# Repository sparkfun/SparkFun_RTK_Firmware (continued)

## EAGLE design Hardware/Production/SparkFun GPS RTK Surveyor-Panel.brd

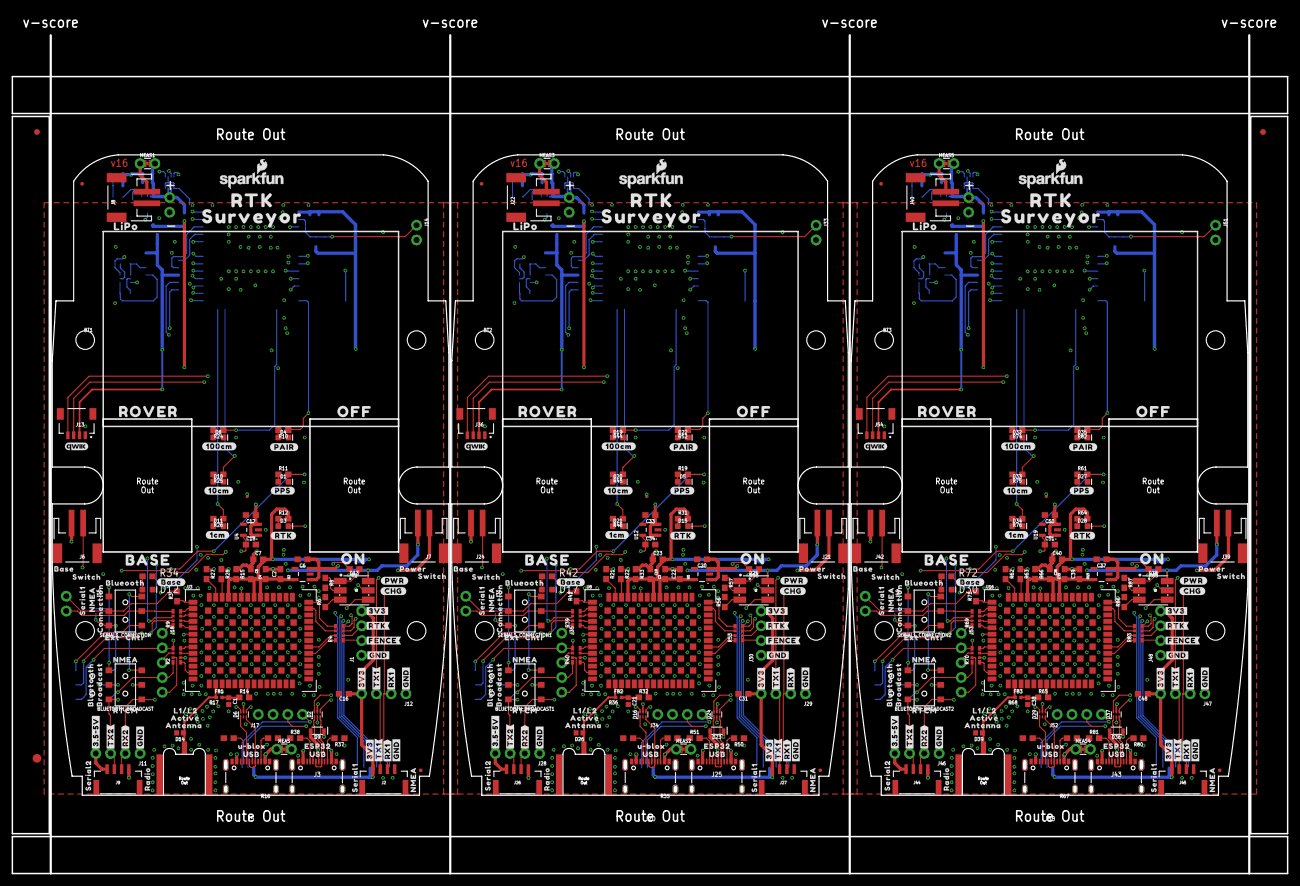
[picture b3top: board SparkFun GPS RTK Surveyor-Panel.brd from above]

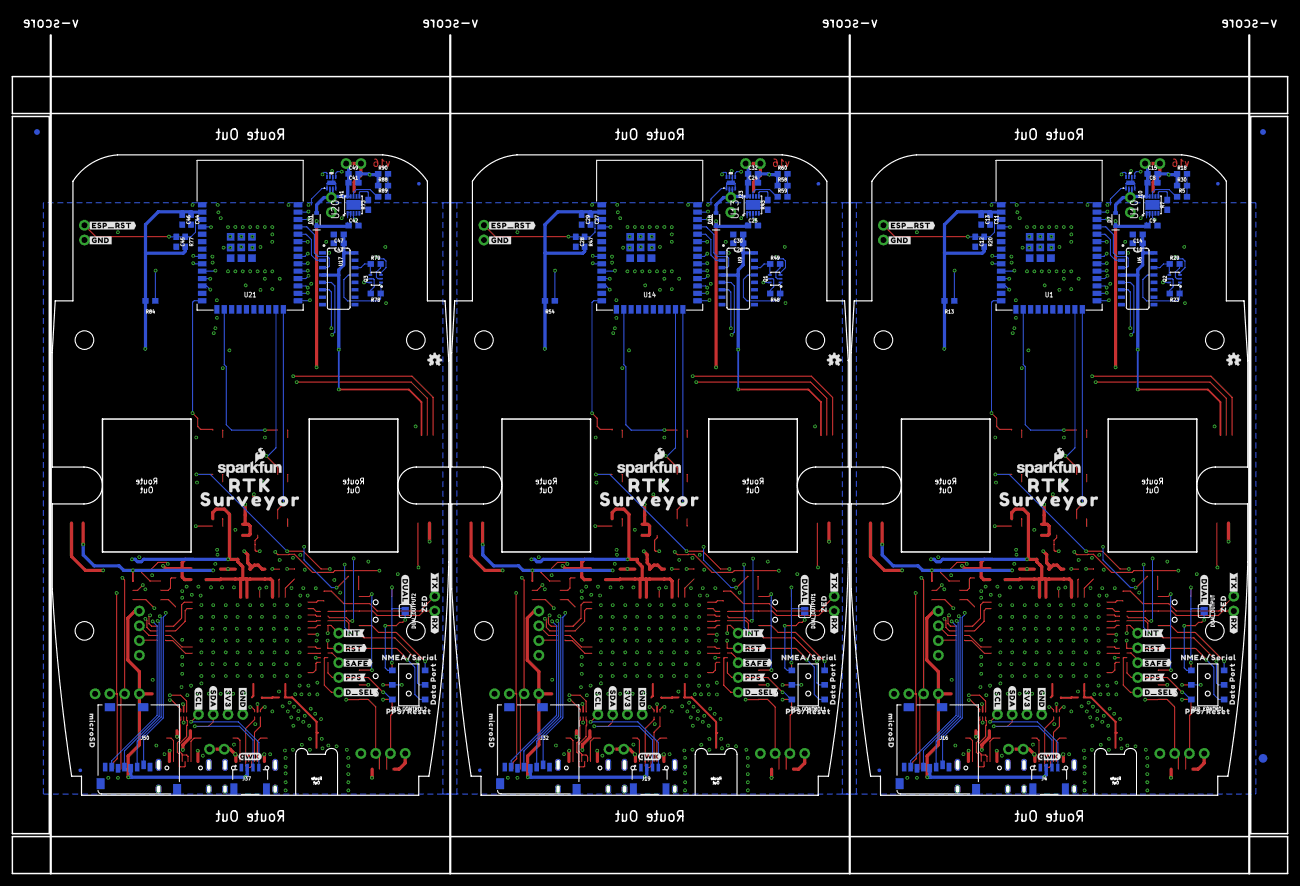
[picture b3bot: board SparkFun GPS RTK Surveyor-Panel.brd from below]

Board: 4 copper layers, 219.3 x 144.2 mm, 588 parts (165 on the bottom side), 285 nets.

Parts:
BLUETOOTH_BROADCAST, BLUETOOTH_BROADCAST1, BLUETOOTH_BROADCAST2: SWITCH_DPDT_SMD_AYZ0202
BT1, BT2, BT3: LIPO-OUTLINE1000; LIPO-1000
C1, C21, C38: 47pF; 0402
C2, C3, C4, C6, C17, C18, C20, C22, C33, C34, C35, C37, C39, C50, C51: 1.0uF; 0603
C5, C7, C11, C12, C13, C15, C16, C19, C23, C27, C28, C29, C31, C32, C36, C40, C44, C45, C46, C48, C49: 0.1uF; 0603
C8, C9, C24, C25, C41, C42: 4.7uF; 0603
C10, C14, C26, C30, C43, C47: 10uF; 0603
D1, D5, D27: Yellow; LED-0603
D2, D6, D16, D24, D29, D37: PRTR5V0U2F; SOT886
D3, D15, D28: WHITE; LED-0603
D4, D22, D35: BLUE; LED-0603
D7, D9, D18, D23, D31, D36: 3A/10V/280mV; SOD-323
D8, D10, D11, D19, D20, D21, D32, D33, D34: GREEN; LED-0603
D12, D17, D30: RED; LED-0603
D13, D25, D38: LED-TRICOLOR-5050
D14, D26, D39: PESD0402; 0402
DUAL_OUTPUT, DUAL_OUTPUT1, DUAL_OUTPUT2: SMT-JUMPER_2_NO_SILK
E1, E2, E3: SMA; SMA-EDGE-SMD
E$1, E$2, E$3, E$4: FIDUCIAL-1X2
E$5, E$6: FIDUCIAL-1.5X3
FB1, FB2, FB3: 2.66Ω; 0402-TIGHT
J1, J11, J12, J28, J29, J30, J46, J47, J48: 1X04_NO_SILK
J2, J9, J26, J27, J44, J45: JST-4-SMD-1.25MM-LOCKING
J3, J5, J20, J25, J38, J43: USB Female Type C Connector; USB-C-16P_4LAYER-PADS
J4, J19, J37: External; JST04_1MM_RA
J6, J24, J42: Start Base; JST-2-SMD
J7, J21, J39: Power Switch; JST-2-SMD
J8, J22, J40: JST-2-SMD
J10, J14, J15, J23, J31, J33, J41, J49, J51: 1X02_NO_SILK
J13, J36, J54: Internal; JST04_1MM_RA
J16, J32, J50: microSD; MICRO-SD-SOCKET
J17, J34, J52: Qwiic Right Angle; 1X04_NO_SILK
J18, J35, J53: 1X05_NO_SILK
JP1, JP2, JP3, JP4, JP5, JP6, JP7, JP8, JP21, JP61, JP71, JP81: FIDUCIALUFIDUCIAL; FIDUCIAL-MICRO
LOGO1, LOGO4, LOGO7: OSHW-LOGOMINI; OSHW-LOGO-MINI
LOGO2, LOGO3, LOGO5, LOGO6, LOGO8, LOGO9: SFE_LOGO_NAME_FLAME.1_INCH; SFE_LOGO_NAME_FLAME_.1
MEAS, MEAS1, MEAS2, MEAS3, MEAS4, MEAS5: COMBO-JUMPER_2_NC_TRACE
Q1, Q2, Q3: MBT3904DW1T1; SC70-6
R1, R55, R85: 4.7k; 0603
R2, R4, R9, R39, R40, R53, R69, R70, R83: 33; 1206_RA
R3, R41, R71: 33; 0603
R5, R59, R89: 0; 0603
R6, R7, R8, R43, R56, R57, R73, R86, R87: 1k; 0603
R10, R12, R31, R34, R42, R52, R64, R72, R82: 330; 0603
R11, R19, R24, R25, R26, R44, R45, R46, R61, R74, R75, R76: 20; 0603
R13, R15, R33, R54, R66, R84: 100k; 0603
R14, R32, R65: 10; 0603
R16, R17, R35, R36, R37, R38, R50, R51, R67, R68, R80, R81: 5.1k; 0603
R18, R20, R23, R29, R47, R48, R49, R60, R77, R78, R79, R90: 10k; 0603
R21, R22, R27, R28, R62, R63: 27; 0603
R30, R58, R88: 150k; 0603
SERIAL1_CONNECTION, SERIAL1_CONNECTION1, SERIAL1_CONNECTION2: SWITCH_DPDT_SMD_AYZ0202
U1, U14, U21: ESP-WROOM-3232D-NARROW; ESP-WROOM-32D-NARROW
U2, U4, U5, U12, U15, U19: 3.3V; SOT23-5
U3, U8, U16: U-BLOX_ZED-F9P; ZED-F9P
U6, U9, U17: CH340C; SO016
U7, U11, U18: MAX17048; DFN-8
U10, U13, U20: MCP73833; DFN-10
U$1, U$38, U$48, U$82, U$98, U$126, U$127, U$169, U$190, U$218, U$219, U$261: #GND#0
U$2, U$30, U$93, U$184, U$185, U$276: QWIIC_4MM
U$3, U$34, U$112, U$114, U$204, U$206: ROCKER_SWITCH
U$4, U$113, U$205: #BASE#0
U$5, U$37, U$47, U$97, U$125, U$166, U$189, U$217, U$258: #3V3#0
U$6, U$99, U$191: ANTENNA0
U$7, U$74, U$173, U$174, U$265, U$266: RTK0
U$8, U$106, U$198: #CHG#0
U$9, U$71, U$100, U$151, U$192, U$243: _SURVEYOR3
U$10, U$101, U$193: #RTK#1
U$11, U$150, U$242: #PPS#0
U$12, U$94, U$186: #RTK#0
U$13, U$15, U$21, U$69, U$75, U$76, U$77, U$78, U$115, U$116, U$149, U$156, U$157, U$158, U$159, U$160, U$207, U$208, U$241, U$248, U$249, U$250, U$251, U$252: LIGHT_PIPE_3MM
U$14, U$152, U$244: #RX#2
U$16, U$153, U$245: ZED0
U$17, U$131, U$223: ##SAFE##5
U$18, U$102, U$194: ACTIVE0
U$19, U$103, U$195: L1#L21
U$20, U$104, U$196: #PAIR#0
U$22, U$117, U$209: BASE2
U$23, U$138, U$230: #3#5#5V#0
U$24, U$95, U$187: #PPS#1
U$25, U$96, U$188: #PWR#2
U$26, U$105, U$197: 1553DBK-ENCLOSURE
U$27, U$107, U$199: LIPO0
U$28, U$130, U$222: ##RST##4
U$29, U$63, U$111, U$147, U$203, U$239: SERIAL10
U$31, U$118, U$210: OFF1
U$32, U$132, U$224: #FENCE#3
U$33, U$133, U$225: #INT#0
U$35, U$108, U$200: U#BLOX0
U$36, U$66, U$109, U$164, U$201, U$256: USB1
U$39, U$121, U$213: #RX2#2
U$40, U$122, U$214: #TX2#1
U$41, U$139, U$231: BLUETOOTH2
U$42, U$119, U$211: ON0
U$43, U$110, U$202: SERIAL20
U$44, U$120, U$212: ROVER3
U$45, U$68, U$123, U$168, U$215, U$260: #RX1#2
U$46, U$65, U$124, U$167, U$216, U$259: #TX1#1
U$49, U$52, U$128, U$141, U$220, U$233: NMEA1
U$50, U$129, U$221: RADIO0
U$51, U$140, U$232: BROADCAST3
U$53, U$142, U$234: RTCM0
U$54, U$134, U$226: BASE0
U$55, U$57, U$135, U$137, U$227, U$229: SWITCH1
U$56, U$136, U$228: POWER0
U$58, U$143, U$235: BLUEOOTH3
U$59, U$144, U$236: CNTR1
U$60, U$172, U$264: #ESP_RST#0
U$61, U$145, U$237: EXT0
U$62, U$146, U$238: NMEA2
U$64, U$148, U$240: CONNECTION1
U$67, U$165, U$257: ESP320
U$70, U$175, U$267: #GND#2
U$72, U$154, U$246: #TX#1
U$73, U$155, U$247: #DUAL#0
U$79, U$161, U$253: #1CM#0
U$80, U$162, U$254: #10CM#1
U$81, U$163, U$255: #100CM#2
U$83, U$170, U$262: MICROSD0
U$84, U$171, U$263: #GND#1
U$85, U$176, U$268: #3V3#2
U$86, U$177, U$269: #SCL#1
U$87, U$178, U$270: #SDA#0
U$88, U$179, U$271: #D_SEL#0
U$89, U$180, U$272: DATA2
U$90, U$181, U$273: PORT3
U$91, U$182, U$274: PPS#RESET0
U$92, U$183, U$275: NMEA#SERIAL1
ZED_CONTROL, ZED_CONTROL1, ZED_CONTROL2: SWITCH_DPDT_SMD_AYZ0202

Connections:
3.3V: C2.1, C4.1, C5.2, C7.2, C10.1, C11.1, C13.1, C14.1, C16.1, J1.4, J2.1, J4.2, J12.4, J13.2, J16.VCC, J17.2, R12.2, R13.2, R15.2, R20.2, U1.2, U2.5, U3.33, U3.34, U3.38, U6.4, U6.16
3.3V1: C3.1, C19.2, C22.1, C23.2, C26.1, C27.1, C29.1, C30.1, C31.1, J19.2, J27.1, J29.4, J30.4, J32.VCC, J34.2, J36.2, R31.2, R33.2, R47.2, R54.2, U5.5, U8.33, U8.34, U8.38, U9.4, U9.16, U14.2
3.3V2: C35.1, C36.2, C39.1, C40.2, C43.1, C44.1, C46.1, C47.1, C48.1, J37.2, J45.1, J47.4, J48.4, J50.VCC, J52.2, J54.2, R64.2, R66.2, R77.2, R84.2, U15.5, U16.33, U16.34, U16.38, U17.4, U17.16, U21.2
5V: C6.1, J7.1, J9.1, J11.4, U2.1, U2.3
5V1: C20.1, J21.1, J26.1, J28.4, U5.1, U5.3
5V2: C37.1, J39.1, J44.1, J46.4, U15.1, U15.3
ANT_VCC: C1.1, FB1.2, R14.1
ANT_VCC1: C21.1, FB2.2, R32.1
ANT_VCC2: C38.1, FB3.2, R65.1
BACKUP: C18.1, U3.36, U4.5
BACKUP1: C34.1, U8.36, U12.5
BACKUP2: C51.1, U16.36, U19.5
CC1: J5.A5, R17.2
CC2: J5.B5, R16.2
CC3: J3.B5, R37.2
CC4: J3.A5, R38.2
CC5: J20.A5, R36.2
CC6: J20.B5, R35.2
CC7: J25.B5, R50.2
CC8: J25.A5, R51.2
CC9: J38.A5, R68.2
CC10: J38.B5, R67.2
CC11: J43.B5, R80.2
CC12: J43.A5, R81.2
CHG_LED: R1.2, U10.3
CHG_LED1: R55.2, U13.3
CHG_LED2: R85.2, U20.3
CHG_THERM1: R5.2, R18.2, R30.2
CHG_THERM2: R58.2, R59.2, R60.2
CHG_THERM3: R88.2, R89.2, R90.2
D+: D6.4, R27.1
D+1: D2.4, U6.5
D+2: D16.4, R21.1
D+3: D24.4, U9.5
D+4: D29.4, R62.1
D+5: D37.4, U17.5
D-: D6.6, R28.1
D-1: D2.6, U6.6
D-2: D16.6, R22.1
D-3: D24.6, U9.6
D-4: D29.6, R63.1
D-5: D37.6, U17.6
ESP32_!DTR: Q2.1, R23.1, U6.13
ESP32_!DTR1: Q1.1, R48.1, U9.13
ESP32_!DTR2: Q3.1, R78.1, U17.13
ESP32_!RTS: Q2.4, R29.1, U6.14
ESP32_!RTS1: Q1.4, R49.1, U9.14
ESP32_!RTS2: Q3.4, R79.1, U17.14
ESP32_EN: C12.1, J14.1, Q2.3, R20.1, U1.3
ESP32_EN1: C28.1, J33.1, Q1.3, R47.1, U14.3
ESP32_EN2: C45.1, J51.1, Q3.3, R77.1, U21.3
ESP32_RXI: U1.34, U6.2
ESP32_RXI1: U9.2, U14.34
ESP32_RXI2: U17.2, U21.34
ESP32_TXO: U1.35, U6.3
ESP32_TXO1: U9.3, U14.35
ESP32_TXO2: U17.3, U21.35
ESP_0/BOOT: Q2.6, U1.25
ESP_0/BOOT1: Q1.6, U14.25
ESP_0/BOOT2: Q3.6, U21.25
ESP_2/LED_1CM: R26.1, U1.24
ESP_2/LED_1CM1: R46.1, U14.24
ESP_2/LED_1CM2: R76.1, U21.24
ESP_4/LED_BASE_STAT: R34.1, U1.26
ESP_4/LED_BASE_STAT1: R42.1, U14.26
ESP_4/LED_BASE_STAT2: R72.1, U21.26
ESP_5/SWITCH_BASE_SELECT: J6.1, U1.29
ESP_5/SWITCH_BASE_SELECT1: J24.1, U14.29
ESP_5/SWITCH_BASE_SELECT2: J42.1, U21.29
ESP_12/LED_BLUETOOTH: R10.1, U1.14
ESP_12/LED_BLUETOOTH1: R52.1, U14.14
ESP_12/LED_BLUETOOTH2: R82.1, U21.14
ESP_13/LED_100CM: R24.1, U1.16
ESP_13/LED_100CM1: R44.1, U14.16
ESP_13/LED_100CM2: R74.1, U21.16
ESP_15/LED_10CM: R25.1, U1.23
ESP_15/LED_10CM1: R45.1, U14.23
ESP_15/LED_10CM2: R75.1, U21.23
ESP_16/BT_RXI: BLUETOOTH_BROADCAST.2, U1.27
ESP_16/BT_RXI1: BLUETOOTH_BROADCAST1.2, U14.27
ESP_16/BT_RXI2: BLUETOOTH_BROADCAST2.2, U21.27
ESP_17/BT_TXO: BLUETOOTH_BROADCAST.5, U1.28
ESP_17/BT_TXO1: BLUETOOTH_BROADCAST1.5, U14.28
ESP_17/BT_TXO2: BLUETOOTH_BROADCAST2.5, U21.28
ESP_18/SD_SCK: J16.SCLK, U1.30
ESP_18/SD_SCK1: J32.SCLK, U14.30
ESP_18/SD_SCK2: J50.SCLK, U21.30
ESP_19/SD_CIPO: J16.DO/DAT0, U1.31
ESP_19/SD_CIPO1: J32.DO/DAT0, U14.31
ESP_19/SD_CIPO2: J50.DO/DAT0, U21.31
ESP_21/SDA: J4.3, J13.3, J17.3, R9.P6, U1.33, U7.8
ESP_21/SDA1: J19.3, J34.3, J36.3, R39.P6, U11.8, U14.33
ESP_21/SDA2: J37.3, J52.3, J54.3, R69.P6, U18.8, U21.33
ESP_22/SCL: J4.4, J13.4, J17.4, R9.P7, U1.36, U7.7
ESP_22/SCL1: J19.4, J34.4, J36.4, R39.P7, U11.7, U14.36
ESP_22/SCL2: J37.4, J52.4, J54.4, R69.P7, U18.7, U21.36
ESP_23/SD_COPI: J16.DI/CMD, U1.37
ESP_23/SD_COPI1: J32.DI/CMD, U14.37
ESP_23/SD_COPI2: J50.DI/CMD, U21.37
ESP_25/SD_!CS!: J16.CS/DAT3, R13.1, U1.10
ESP_25/SD_!CS!1: J32.CS/DAT3, R54.1, U14.10
ESP_25/SD_!CS!2: J50.CS/DAT3, R84.1, U21.10
ESP_26/ZED_TX_READY: J18.1, R9.P8, U1.11
ESP_26/ZED_TX_READY1: J35.1, R39.P8, U14.11
ESP_26/ZED_TX_READY2: J53.1, R69.P8, U21.11
ESP_26/ZED_TX_READY_LV: R9.P1, U3.46
ESP_26/ZED_TX_READY_LV1: R39.P1, U8.46
ESP_26/ZED_TX_READY_LV2: R69.P1, U16.46
ESP_27/ZED_!RESET!: J18.2, R2.P5, U1.12, ZED_CONTROL.4
ESP_27/ZED_!RESET!1: J35.2, R40.P5, U14.12, ZED_CONTROL1.4
ESP_27/ZED_!RESET!2: J53.2, R70.P5, U21.12, ZED_CONTROL2.4
ESP_27/ZED_!RESET!_LV: R2.P4, U3.49
ESP_27/ZED_!RESET!_LV1: R40.P4, U8.49
ESP_27/ZED_!RESET!_LV2: R70.P4, U16.49
ESP_32/PWR_LVL_RED: D13.5, U1.8
ESP_32/PWR_LVL_RED1: D25.5, U14.8
ESP_32/PWR_LVL_RED2: D38.5, U21.8
ESP_33/PWR_LVL_GRN: D13.4, U1.9
ESP_33/PWR_LVL_GRN1: D25.4, U14.9
ESP_33/PWR_LVL_GRN2: D38.4, U21.9
ESP_36/BATT_ALRT: U1.4, U7.5
ESP_36/BATT_ALRT1: U11.5, U14.4
ESP_36/BATT_ALRT2: U18.5, U21.4
ESP_D1+: D2.3, J3.A6, J3.B6
ESP_D1+1: D24.3, J25.A6, J25.B6
ESP_D1+2: D37.3, J43.A6, J43.B6
ESP_D1-: D2.1, J3.A7, J3.B7
ESP_D1-1: D24.1, J25.A7, J25.B7
ESP_D1-2: D37.1, J43.A7, J43.B7
EXTERNAL_SERIAL1_RXI: SERIAL1_CONNECTION.4, ZED_CONTROL.6
EXTERNAL_SERIAL1_RXI1: SERIAL1_CONNECTION1.4, ZED_CONTROL1.6
EXTERNAL_SERIAL1_RXI2: SERIAL1_CONNECTION2.4, ZED_CONTROL2.6
EXTERNAL_SERIAL1_RXI/ZED_!RESET!: J2.3, J12.2, ZED_CONTROL.5
EXTERNAL_SERIAL1_RXI/ZED_!RESET!1: J27.3, J29.2, ZED_CONTROL1.5
EXTERNAL_SERIAL1_RXI/ZED_!RESET!2: J45.3, J47.2, ZED_CONTROL2.5
EXTERNAL_SERIAL1_TXO: DUAL_OUTPUT.2, SERIAL1_CONNECTION.1, ZED_CONTROL.3
EXTERNAL_SERIAL1_TXO1: DUAL_OUTPUT1.2, SERIAL1_CONNECTION1.1, ZED_CONTROL1.3
EXTERNAL_SERIAL1_TXO2: DUAL_OUTPUT2.2, SERIAL1_CONNECTION2.1, ZED_CONTROL2.3
EXTERNAL_SERIAL1_TXO/PPS: J2.2, J12.3, ZED_CONTROL.2
EXTERNAL_SERIAL1_TXO/PPS1: J27.2, J29.3, ZED_CONTROL1.2
EXTERNAL_SERIAL1_TXO/PPS2: J45.2, J47.3, ZED_CONTROL2.2
FENCE_LV: R4.P8, U3.19
FENCE_LV1: R53.P8, U8.19
FENCE_LV2: R83.P8, U16.19
GND: C1.2, C2.2, C4.2, C5.1, C6.2, C7.1, C8.2, C9.2, C10.2, C11.2, C12.2, C13.2, C14.2, C15.2, C16.2, C17.2, C18.2, D1.C, D2.2, D4.C, D6.2, D8.C, D10.C, D11.C, D12.C, D14.2, E1.GND@0, E1.GND@1, J1.1, J2.4, J3.GND, J3.GND2, J3.SHLD1, J3.SHLD2, J3.SHLD3, J3.SHLD4, J4.1, J5.GND, J5.GND2, J5.SHLD1, J5.SHLD2, J5.SHLD3, J5.SHLD4, J6.2, J8.1, J9.4, J10.2, J11.1, J12.1, J13.1, J14.2, J16.CD1, J16.GND, J16.GND1, J16.GND3, J17.1, R6.2, R7.1, R8.2, R15.1, R16.1, R17.1, R18.1, R30.1, R37.1, R38.1, U1.1, U1.15, U1.38, U1.GND1, U1.GNDT1, U1.GNDT2, U1.GNDT3, U1.GNDT4, U1.GNDT5, U1.GNDT6, U1.GNDT7, U1.GNDT8, U2.2, U3.1, U3.3, U3.12, U3.14, U3.32, U3.37, U3.41, U3.48, U3.55, U3.56, U3.57, U3.58, U3.59, U3.60, U3.61, U3.62, U3.63, U3.64, U3.65, U3.66, U3.67, U3.68, U3.69, U3.70, U3.71, U3.72, U3.73, U3.74, U3.75, U3.76, U3.77, U3.78, U3.79, U3.80, U3.81, U3.82, U3.83, U3.84, U3.85, U3.86, U3.87, U3.88, U3.89, U3.90, U3.91, U3.92, U3.93, U3.94, U3.95, U3.96, U3.97, U3.98, U3.99, U3.100, U3.101, U3.102, U4.2, U6.1, U7.1, U7.4, U7.6, U7.9, U10.5, U10.11
GND1: C3.2, C19.1, C20.2, C21.2, C22.2, C23.1, C24.2, C25.2, C26.2, C27.2, C28.2, C29.2, C30.2, C31.2, C32.2, C33.2, C34.2, D5.C, D16.2, D17.C, D19.C, D20.C, D21.C, D22.C, D24.2, D26.2, E2.GND@0, E2.GND@1, J19.1, J20.GND, J20.GND2, J20.SHLD1, J20.SHLD2, J20.SHLD3, J20.SHLD4, J22.1, J23.2, J24.2, J25.GND, J25.GND2, J25.SHLD1, J25.SHLD2, J25.SHLD3, J25.SHLD4, J26.4, J27.4, J28.1, J29.1, J30.1, J32.CD1, J32.GND, J32.GND1, J32.GND3, J33.2, J34.1, J36.1, R33.1, R35.1, R36.1, R43.1, R50.1, R51.1, R56.2, R57.2, R58.1, R60.1, U5.2, U8.1, U8.3, U8.12, U8.14, U8.32, U8.37, U8.41, U8.48, U8.55, U8.56, U8.57, U8.58, U8.59, U8.60, U8.61, U8.62, U8.63, U8.64, U8.65, U8.66, U8.67, U8.68, U8.69, U8.70, U8.71, U8.72, U8.73, U8.74, U8.75, U8.76, U8.77, U8.78, U8.79, U8.80, U8.81, U8.82, U8.83, U8.84, U8.85, U8.86, U8.87, U8.88, U8.89, U8.90, U8.91, U8.92, U8.93, U8.94, U8.95, U8.96, U8.97, U8.98, U8.99, U8.100, U8.101, U8.102, U9.1, U11.1, U11.4, U11.6, U11.9, U12.2, U13.5, U13.11, U14.1, U14.15, U14.38, U14.GND1, U14.GNDT1, U14.GNDT2, U14.GNDT3, U14.GNDT4, U14.GNDT5, U14.GNDT6, U14.GNDT7, U14.GNDT8
GND2: C35.2, C36.1, C37.2, C38.2, C39.2, C40.1, C41.2, C42.2, C43.2, C44.2, C45.2, C46.2, C47.2, C48.2, C49.2, C50.2, C51.2, D27.C, D29.2, D30.C, D32.C, D33.C, D34.C, D35.C, D37.2, D39.2, E3.GND@0, E3.GND@1, J37.1, J38.GND, J38.GND2, J38.SHLD1, J38.SHLD2, J38.SHLD3, J38.SHLD4, J40.1, J41.2, J42.2, J43.GND, J43.GND2, J43.SHLD1, J43.SHLD2, J43.SHLD3, J43.SHLD4, J44.4, J45.4, J46.1, J47.1, J48.1, J50.CD1, J50.GND, J50.GND1, J50.GND3, J51.2, J52.1, J54.1, R66.1, R67.1, R68.1, R73.1, R80.1, R81.1, R86.2, R87.2, R88.1, R90.1, U15.2, U16.1, U16.3, U16.12, U16.14, U16.32, U16.37, U16.41, U16.48, U16.55, U16.56, U16.57, U16.58, U16.59, U16.60, U16.61, U16.62, U16.63, U16.64, U16.65, U16.66, U16.67, U16.68, U16.69, U16.70, U16.71, U16.72, U16.73, U16.74, U16.75, U16.76, U16.77, U16.78, U16.79, U16.80, U16.81, U16.82, U16.83, U16.84, U16.85, U16.86, U16.87, U16.88, U16.89, U16.90, U16.91, U16.92, U16.93, U16.94, U16.95, U16.96, U16.97, U16.98, U16.99, U16.100, U16.101, U16.102, U17.1, U18.1, U18.4, U18.6, U18.9, U19.2, U20.5, U20.11, U21.1, U21.15, U21.38, U21.GND1, U21.GNDT1, U21.GNDT2, U21.GNDT3, U21.GNDT4, U21.GNDT5, U21.GNDT6, U21.GNDT7, U21.GNDT8
GPS_ANT1: D14.1, E1.SIG, FB1.1, U3.2
GPS_ANT2: D26.1, E2.SIG, FB2.1, U8.2
GPS_ANT3: D39.1, E3.SIG, FB3.1, U16.2
LIPO_RAW: J8.2, MEAS1.1, MEAS1.3
LIPO_RAW1: J22.2, MEAS3.1, MEAS3.3
LIPO_RAW2: J40.2, MEAS5.1, MEAS5.3
unnamed: D3.A, R12.1
unnamed: D1.A, R11.1
unnamed: D4.A, R10.2
unnamed: J5.VBUS1, J5.VBUS2, MEAS.1, MEAS.3
unnamed: R5.1, U10.8
unnamed: D13.1, R1.1
unnamed: D13.3, R6.1
unnamed: D13.2, R8.1
unnamed: D5.A, R19.1
unnamed: R21.2, U8.40
unnamed: R27.2, U3.40
unnamed: R28.2, U3.39
unnamed: R14.2, U3.7
unnamed: R22.2, U8.39
unnamed: D15.A, R31.1
unnamed: R32.2, U8.7
unnamed: D17.A, R42.2
unnamed: D19.A, R44.2
unnamed: D20.A, R45.2
unnamed: D21.A, R46.2
unnamed: Q1.5, R48.2
unnamed: Q1.2, R49.2
unnamed: D23.A, J25.VBUS1, J25.VBUS2
unnamed: Q2.5, R23.2
unnamed: Q2.2, R29.2
unnamed: D8.A, R24.2
unnamed: D10.A, R25.2
unnamed: D22.A, R52.2
unnamed: D11.A, R26.2
unnamed: D12.A, R34.2
unnamed: J20.VBUS1, J20.VBUS2, MEAS2.1, MEAS2.3
unnamed: D9.A, J3.VBUS1, J3.VBUS2
unnamed: R59.1, U13.8
unnamed: D25.1, R55.1
unnamed: D25.3, R56.1
unnamed: D25.2, R57.1
unnamed: D27.A, R61.1
unnamed: R62.2, U16.40
unnamed: R63.2, U16.39
unnamed: D28.A, R64.1
unnamed: R65.2, U16.7
unnamed: D30.A, R72.2
unnamed: D32.A, R74.2
unnamed: D33.A, R75.2
unnamed: D34.A, R76.2
unnamed: Q3.5, R78.2
unnamed: Q3.2, R79.2
unnamed: D36.A, J43.VBUS1, J43.VBUS2
unnamed: D35.A, R82.2
unnamed: J38.VBUS1, J38.VBUS2, MEAS4.1, MEAS4.3
unnamed: R89.1, U20.8
unnamed: D38.1, R85.1
unnamed: D38.3, R86.1
unnamed: D38.2, R87.1
NMEA-RX: BLUETOOTH_BROADCAST.6, SERIAL1_CONNECTION.6
NMEA-RX1: BLUETOOTH_BROADCAST1.6, SERIAL1_CONNECTION1.6
NMEA-RX2: BLUETOOTH_BROADCAST2.6, SERIAL1_CONNECTION2.6
NMEA-TX: BLUETOOTH_BROADCAST.3, DUAL_OUTPUT.1, SERIAL1_CONNECTION.3
NMEA-TX1: BLUETOOTH_BROADCAST1.3, DUAL_OUTPUT1.1, SERIAL1_CONNECTION1.3
NMEA-TX2: BLUETOOTH_BROADCAST2.3, DUAL_OUTPUT2.1, SERIAL1_CONNECTION2.3
PPS: R2.P1, U3.53
PPS1: R40.P1, U8.53
PPS2: R70.P1, U16.53
PROG1: R7.2, U10.6
PROG2: R43.2, U13.6
PROG3: R73.2, U20.6
RTK_LV: R4.P7, U3.20
RTK_LV1: R53.P7, U8.20
RTK_LV2: R83.P7, U16.20
RX2_LV: R4.P6, U3.26
RX2_LV1: R53.P6, U8.26
RX2_LV2: R83.P6, U16.26
RXLV: R9.P4, U3.43
RXLV1: R39.P4, U8.43
RXLV2: R69.P4, U16.43
SCL_LV: R9.P2, U3.45
SCL_LV1: R39.P2, U8.45
SCL_LV2: R69.P2, U16.45
SDA_LV: R9.P3, U3.44
SDA_LV1: R39.P3, U8.44
SDA_LV2: R69.P3, U16.44
TX2_LV: R4.P5, U3.27
TX2_LV1: R53.P5, U8.27
TX2_LV2: R83.P5, U16.27
TXLV: R3.1, U3.42
TXLV1: R41.1, U8.42
TXLV2: R71.1, U16.42
UNP_D+: D6.3, J5.A6, J5.B6
UNP_D+1: D16.3, J20.A6, J20.B6
UNP_D+2: D29.3, J38.A6, J38.B6
UNP_D-: D6.1, J5.A7, J5.B7
UNP_D-1: D16.1, J20.A7, J20.B7
UNP_D-2: D29.1, J38.A7, J38.B7
VIN: C9.1, D2.5, D6.5, D7.C, D9.C, D13.6, J7.2, MEAS.2, MEAS.4, U10.1, U10.2
VIN1: C25.1, D16.5, D18.C, D23.C, D24.5, D25.6, J21.2, MEAS2.2, MEAS2.4, U13.1, U13.2
VIN2: C42.1, D29.5, D31.C, D36.C, D37.5, D38.6, J39.2, MEAS4.2, MEAS4.4, U20.1, U20.2
V_BATT: C8.1, C15.1, C17.1, D7.A, J10.1, MEAS1.2, MEAS1.4, U4.1, U4.3, U7.2, U7.3, U10.9, U10.10
V_BATT1: C24.1, C32.1, C33.1, D18.A, J23.1, MEAS3.2, MEAS3.4, U11.2, U11.3, U12.1, U12.3, U13.9, U13.10
V_BATT2: C41.1, C49.1, C50.1, D31.A, J41.1, MEAS5.2, MEAS5.4, U18.2, U18.3, U19.1, U19.3, U20.9, U20.10
ZED-RXI1: J15.2, R9.P5, SERIAL1_CONNECTION.5
ZED-RXI2: BLUETOOTH_BROADCAST.4, J9.3, J11.2, R4.P3
ZED-RXI3: BLUETOOTH_BROADCAST1.4, J26.3, J28.2, R53.P3
ZED-RXI4: J31.2, R39.P5, SERIAL1_CONNECTION1.5
ZED-RXI5: BLUETOOTH_BROADCAST2.4, J44.3, J46.2, R83.P3
ZED-RXI6: J49.2, R69.P5, SERIAL1_CONNECTION2.5
ZED-TXO1: J15.1, R3.2, SERIAL1_CONNECTION.2
ZED-TXO2: BLUETOOTH_BROADCAST.1, J9.2, J11.3, R4.P4
ZED-TXO3: J31.1, R41.2, SERIAL1_CONNECTION1.2
ZED-TXO4: BLUETOOTH_BROADCAST1.1, J26.2, J28.3, R53.P4
ZED-TXO5: J49.1, R71.2, SERIAL1_CONNECTION2.2
ZED-TXO6: BLUETOOTH_BROADCAST2.1, J44.2, J46.3, R83.P4
ZED_!SAFE!: J18.3, R2.P6
ZED_!SAFE!1: J35.3, R40.P6
ZED_!SAFE!2: J53.3, R70.P6
ZED_!SAFE!_LV: R2.P3, U3.50
ZED_!SAFE!_LV1: R40.P3, U8.50
ZED_!SAFE!_LV2: R70.P3, U16.50
ZED_D_SEL: J18.5, R2.P7
ZED_D_SEL1: J35.5, R40.P7
ZED_D_SEL2: J53.5, R70.P7
ZED_D_SEL_LV: R2.P2, U3.47
ZED_D_SEL_LV1: R40.P2, U8.47
ZED_D_SEL_LV2: R70.P2, U16.47
ZED_FENCE_STAT: J1.2, R4.P1
ZED_FENCE_STAT1: J30.2, R53.P1
ZED_FENCE_STAT2: J48.2, R83.P1
ZED_PPS_STAT: J18.4, R2.P8, R11.2, ZED_CONTROL.1
ZED_PPS_STAT1: J35.4, R19.2, R40.P8, ZED_CONTROL1.1
ZED_PPS_STAT2: J53.4, R61.2, R70.P8, ZED_CONTROL2.1
ZED_RTK_STAT: D3.C, J1.3, R4.P2
ZED_RTK_STAT1: D15.C, J30.3, R53.P2
ZED_RTK_STAT2: D28.C, J48.3, R83.P2

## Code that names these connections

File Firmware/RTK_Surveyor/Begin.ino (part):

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        pin_GNSS_CS = 5;
        pin_GNSS_TimePulse = 25;
        pin_adc39 = 39;
        pin_zed_tx_ready = 34;
        pin_microSD_CardDetect = 36;
        pin_Ethernet_Interrupt = 33;
        pin_setupButton = 0;
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        {
            // Detect RTK Expresses (v1.3 and below) that do not have an accel or device ID resistors

            // On a Surveyor, pin 34 is not connected. On Express, 34 is connected to ZED_TX_READY
            const int pin_ZedTxReady = 34;
            uint16_t pinValue = analogReadMilliVolts(pin_ZedTxReady);
            log_d("Alternate ID pinValue (mV): %d\r\n", pinValue); // Surveyor = 142 to 152, //Express = 3129
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        pin_bluetoothStatusLED = 12;
        pin_setupButton = 5;
        pin_microSD_CS = 25;
        pin_zed_tx_ready = 26;
        pin_zed_reset = 27;
        pin_batteryLevel_alert = 36;

        // Bug in ZED-F9P v1.13 firmware causes RTK LED to not light when RTK Floating with SBAS on.
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                    &ButtonCheckTaskHandle); // Task handle
}

// Setup the timepulse output on the PPS pin for external triggering
// Setup TM2 time stamp input as need
bool beginExternalTriggers()
{
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
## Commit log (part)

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2023-08-31 Use Arduino CLI to build the RTK Surveyor firmware
2023-09-01 init captive portal
2023-09-02 Common tail pointer manipulation when discarding ring buffer data
2023-09-02 Discard the oldest data in the ring buffer
2023-09-02 Support rebooting after uptime reaches a number of seconds
2023-09-05 Fix typo
    From PR #638
2023-09-06 init settings, problem with web config
2023-09-07 Docs: Fix GSA typo
2023-09-07 fix web config pvt enabe
2023-09-07 Add RTK_FACET_LBAND_DIRECT variant
2023-09-07 Add L-Band direct variant to basic functions
2023-09-07 Configure NEO for direct connect, based on variant.
2023-09-07 Limit 'Givenname' to 50 chars, limit of PointPerfect API
2023-09-07 Re-enable printCurrentConditions
2023-09-07 VS Code format/whitespace only change
2023-09-07 Explicitly state Bluetooth type in menus
2023-09-08 add pvtUdpServer
2023-09-08 default debugPvtUdpServer to false
2023-09-08 Use an array to discard data, overhead during discard only
2023-09-09 remove console logs
2023-09-12 init NetworkUDP.h
2023-09-12 Remove place-holder html to avoid double parsing of DTM message.
    Fix for #646,
2023-09-12 Add missing NTP function for compile guards.
2023-09-14 NTRIP Client: Reset attempt count & timeout after long connection
2023-09-14 NTRIP Client: Force backoff when the client retries
2023-09-14 NTRIP Server: Reset attempt count & timeout after long connection
2023-09-14 Remove powerButtonFiltering setting. Use firmware version to determine test.
2023-09-14 Add not compiled print to startWebServer
2023-09-14 Increase version
2023-09-14 Correct caster response to banning. Add sandbox test.
    Caster responds with '200' even when reporting ban or sourcetable. Correct the logic that tests for that. Also, added test for 'sandbox'.
2023-09-14 Increase aggressiveness of reconnect timeout
2023-09-14 Convert stray Serial.prints.
2023-09-14 Fall back to AP mode for Config if local WiFi unavailable
    Fix for issue #611
2023-09-17 Correct IP display if forced AP Config.
2023-09-18 menuPP: Fix no friendly WiFi infinite loop
2023-09-19 OTA: Fix version number passed to ota.CheckForOTAUpdate
2023-09-19 Load partial settings after platform is dected
    So that setSettingsFileName has correct info. Reversion of [this commit](https://github.com/sparkfun/SparkFun_RTK_Firmware/commit/718f07c245f7a7f318f10073837cd3de0531091e#diff-b1c05b3c11dc036b5248d55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
2023-09-19 menuSystem: Fix typo in debug menu item 26
2023-09-20 menuSystem: Fix Wifi IP Address entry in network menu
2023-09-21 Docs: Fix WiFi NTRIP Client note.
2023-09-25 States: Eliminate infinite loop in STATE_KEYS_WIFI_STARTED
2023-09-26 Turn off L-Band if RTCM is received.
    Testing shows that the ZED gets confused (positional accuracy bounces around a lot) if both PMP and RTCM are fed into the ZED.
2023-09-26 Correctly handle L-Band restart if RTK Fix is lost
2023-09-26 States: Turn off WiFi before entering STATE_KEYS_WIFI_TIMEOUT
2023-09-26 Add needed function for WiFi compile guard
2023-09-26 Only print SD report once SD is online
2023-09-26 Remove state STATE_KEYS_PROVISION_WIFI_TIMEOUT
2023-09-27 If BT was off before provisioning, don't start it
    Fix #678
2023-09-27 Increase maxTries to original to reduce false positives.
2023-09-28 menuPP: Print compiler & runtime warning when using the DEVELOPER_TOKEN
2023-09-28 menuPP: Add menu item to clear the keys
2023-09-28 menuFirmware: Switch log_d to systemPrintln to announce firmware status
2023-09-29 Erase GNSS receiver position during factory reset.
2023-09-29 Add settings for auto firmware update
2023-09-29 menuFirmware: Change automatic firmware update settings
2023-09-29 settings.h: Add tables to support automatic firmware update
2023-09-29 RTK_Surveyor: Call updateFirmware in the loop
2023-09-29 menuFirmware: Start and stop the WiFi network for firmware updates
2023-09-29 menuFirmware: Firmware update checks for the new firmware version
2023-10-02 Add discardPvtUdpServerBytes to developer.ino to enable WiFi guard
2023-10-02 Fix bad image link
2023-10-11 WiFi: Simplify wifiIsNeeded
2023-10-11 Call the OTA update routine
2023-10-11 OTA: Start and stop the network
2023-10-11 OTA: SSL client reading JSON file
2023-10-12 OtaClient: Automatic firmware download over WiFi
    Automatic firmware updates uses WiFi to check the SparkFun firmware
    release site for a new version of the released firmware. An update
    occurs when:
    * The current version of the firmware is less than the version on the
    SparkFun site
    * The current version is a debug version (starts with 'd')
2023-10-12 Fix compiles with and without COMPILE_ETHERNET and COMPILE_WIFI
2023-10-12 OTA: Support periodic state prints
2023-10-13 OTA: Conditionally display the OTA minutes value in the firmware menu
2023-10-13 OTA: Add some documentation
2023-10-15 OTA: Add OTA: prefix to output
2023-10-15 OTA: Move network checks to beginning of state
2023-10-15 OTA: Allow partial writes to flash
2023-10-16 OTA: Timeout and retry the binary file transfers
2023-10-17 Network: Delay reconnection attempts only when connection is successful
2023-10-18 Handle free pointer in pointperfectProvisionDevice
2023-10-18 Change updateLBand to check systemState
    Avoids immediate ZED reset as a unit moves from 3D fix to RTK Float.
2023-10-18 Whitespace changes
2023-10-19 Remove duration from thingstreamEpochToGPSEpoch
2023-10-19 Add debug/print helper functions
2023-10-19 Use helper functions to print
2023-10-19 Set next duration to 28 days.
    Don't assume the current duration is the next duration.
2023-10-19 Get keys once primary key has expired
2023-10-19 Add SSLClient library to workflow
2023-10-19 Limit device name length during BLE.
2023-10-19 Debug Point Perfect certificate management
2023-10-19 menuPP: Properly validate the private key
2023-10-21 Network clients start and stop depending upon operating modes
    Define the RTK operating modes and set these modes in States.ino.
    For each network user:
    * Add a bit mask specifying which modes the network user is active
    * Stop the network user when the enable or mode changes
    * Start the network user when the mode and enable are set
2023-10-22 Break out the GPS message parser
2023-10-22 Fix typo in ADC voltage ID value
2023-10-26 Better document the resistor divider and the ADC ID value
2023-10-26 Facet L-Band Direct: Change display name from FACET LB to Facet LD
2023-10-26 Add debugLBand to NVM
2023-10-26 Correctly print key date and duration
2023-10-27 Add enableCaptivePortal setting. Set to on as default.
2023-10-27 Fix typo
2023-10-27 Add prefix to profile names
    Fix for #670
2023-10-27 Docs: Update OTA image
2023-10-27 Enable SPARTN over USB
    Fix for #713
2023-11-02 Add print during resistor ID check
2023-12-12 Increase default Bluetooth SPP RX buffer
    Fix #733
2023-12-12 Use modern sync() for compatibility with newer ESP cores.
2023-12-12 Add ability to disable ZED USB port
    Fix #734
2023-12-13 Add GetKeys menu to display on L-Band units.
2023-12-13 Convert Serial prints to systemPrints.
2023-12-13 Fix display sort order
2023-12-13 Correctly start/stop Bluetooth during key update
    Fix #738
2023-12-19 Whitespace format
2023-12-19 Output "Account Expired" if device is detected as deactivated.
2023-12-27 Add debugWiFiConfig. Change log_ds to prints.
2023-12-27 L-Band: Display not listed if whitelist error is seen.
2023-12-27 Change to station before setting WiFi protocols.
    Prior to this, the WiFi radio could be on, but be in AP mode. If the old code ran, the protocols would not get set correctly because of mode was not correctly set to station (getMode != WIFI_OFF).
2023-12-27 Display RTK Config when local WiFi config fails.
2023-12-27 L-Band: Always print the HTTP response error.
2023-12-27 Increase major version number
    It's time, and will fix #742
2023-12-27 L-Band: Fix MQTT key checking
2023-12-27 Remove defunct Vector corrections provider.
2023-12-29 Add core load test sketch
2023-12-30 Rename variable to settingString
2023-12-30 Rename settingString
2023-12-30 Typo
2024-01-03 added new coverage regions for the point one service
2024-01-04 Add Premium Positioning service
2024-01-10 Docs: Fix typo
2024-01-11 Update test sketch with new variants
2024-01-11 Deployed f915402 with MkDocs version: 1.5.3
2024-01-19 Network: Fix issue 749, networkUserClose failed to get network
2024-04-26 Update image of display board with friction fit connector
    Fix forum issue: https://forum.sparkfun.com/posting.php?f=116&mode=reply&t=60066&sid=9aba890dffeda8f36f667e6ccf100418
2024-04-30 Increase the RTCM transmit timeout from 3 seconds to 15 seconds
    Allows NTRIP server connection failures to occur without breaking the
    NTRIP server connection to another server.
2024-04-30 Properly separate WiFi state values from WiFi mode values
2024-04-30 Switch to using ntripServerArray
2024-04-30 Move NTRIP server data into the data structure
2024-04-30 Add unique values for each of the NTRIP server settings
2024-05-10 Elevate Bluetooth SPP buffer full error.
2024-05-10 Move logo display after power on check
    Fix #762
2024-06-05 Resolve #769. Add settings.geographicRegion. Delete settings.LBandFreq
2024-06-05 Better key distribution topic extraction
2024-06-05 Fix for #771
2024-06-06 Correct negative DDMMSS.sss in main.js
2024-06-06 Add printRTKState
2024-06-06 Check coordinate types are the same in menuBase
2024-06-06 Comment coordinate type console logs in main.js
2024-06-06 ntripServer settings - add missing underscores etc.
2024-06-06 Better debug in ntripServerProcessRTCM - equal printing of servers 0 and 1
2024-06-06 Increase name array size for NTRIP CasterHost etc.
2024-06-07 Better NTRIP debugging
2024-06-10 Prevent NtripServer from disabling settings.enableNtripServer
2024-06-10 Cosmetic: correct ntripServerStop in Developer.ino
2024-06-11 Docs: Update GIS software
2024-06-11 Docs: Add Windows GIS
2024-06-11 Deployed 7e8fd85 with MkDocs version: 1.6.0
2024-06-14 Correct web config NTRIP Server validation
    Add TCP / UDP Configuration button
    Add TCP Client Host entry
    Delete Ethernet TCP Client settings
2024-07-22 Add ZED firmware test to system test display
2024-08-09 Increase BleSerial version
2024-08-20 Docs: Add Onocoy corrections
2024-09-12 Docs: Add to iOS GIS apps
2024-09-13 Docs: Fix whitespace
2024-12-23 Fix wrong survey-in time limit in help text
    Reference station doesn't accept values above 600 seconds for survey-in while the help text suggests values up to and including 900 seconds are acceptable.
2025-01-17 Include .elf in non-release-build
2025-01-23 doc/menu_ports.md: Note that the radio port is F9P UART2.
2025-01-24 Update repair.md
    Move the warning about fingerprints on the antenna earlier in the document, so that the reader will see it in time.
    Add a photo showing the correct orientation of the antenna within the enclosure.
2025-02-21 Update PP L-Band coverage
2025-07-11 Increase mark altitude resolution
    Resolves #792
2025-07-17 make log message match function name
2025-07-23 Add L-Band service discontinuation notice
2025-08-29 Update BleSerial version comment
2025-08-29 Remove unused localIp
2025-09-02 Resolve #632
2025-09-03 Now we're getting somewhere...!
2025-09-04 Instantiate the clients inside the server - working on Ethernet!
2025-09-04 Add settings.displayServerIP
2025-09-05 Better server display
2025-09-05 Rename pvtUdpServerRuning
2025-09-05 Replace redundant code
2025-09-09 Add MDNS comments
2025-09-09 Keep WiFi alive when no PvtServer clients are conected
2025-09-09 Move Event and ARP writing into handleGnssDataTask
    Write all available data to SD, then write Event and/or ARP
2025-10-27 Increase size of temp in displayMessageFont - resolves #800
2025-10-27 Correct comments re. default TCP port - 2948 not 2947
2025-10-27 Add compile_with_docker.bat
2025-10-28 Deployed 7393fae with MkDocs version: 1.6.1
2025-11-05 Describe WiFi configuration as choice betwen AP and STA
    Improve readability of WiFi configuration by using industry standard terminology AP and STA.
